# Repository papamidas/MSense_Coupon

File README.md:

# MSense_Coupon
Coupon for measuring moisture in soil

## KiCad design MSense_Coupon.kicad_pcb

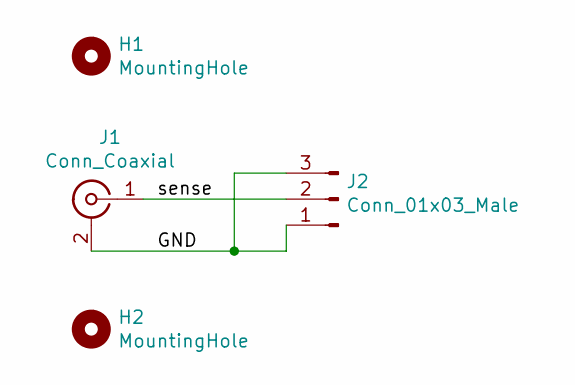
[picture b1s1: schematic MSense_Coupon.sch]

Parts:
H1, H2: MountingHole; MountingHole_3.2mm_M3
J1: Conn_Coaxial; SMA_Amphenol_132289_EdgeMount
J2: Conn_01x03_Male; PinHeader_1x03_P2.54mm_Vertical

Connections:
/GND: H1.1, H2.1, J1.2 (Ext), J2.1, J2.3
/sense: J1.1 (In), J2.2

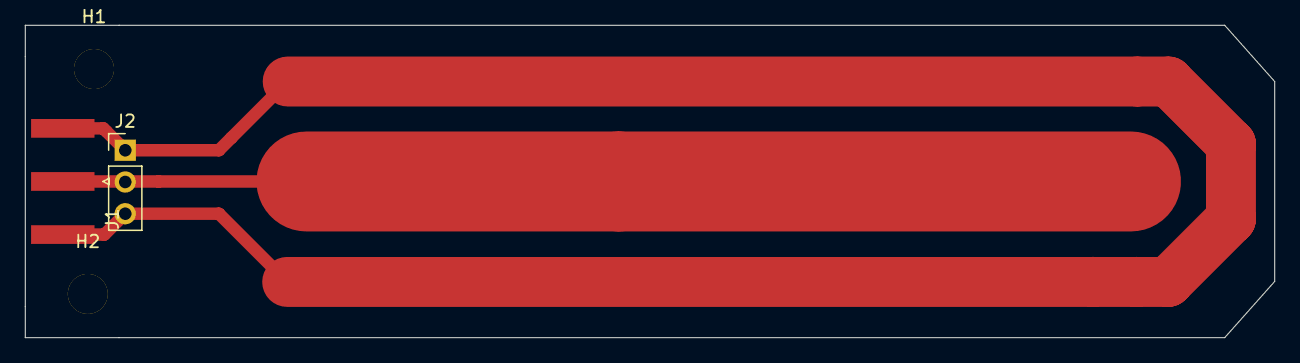
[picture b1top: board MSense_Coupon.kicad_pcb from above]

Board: 2 copper layers, 100.0 x 25.0 mm, 4 parts (0 on the bottom side), 2 nets.
